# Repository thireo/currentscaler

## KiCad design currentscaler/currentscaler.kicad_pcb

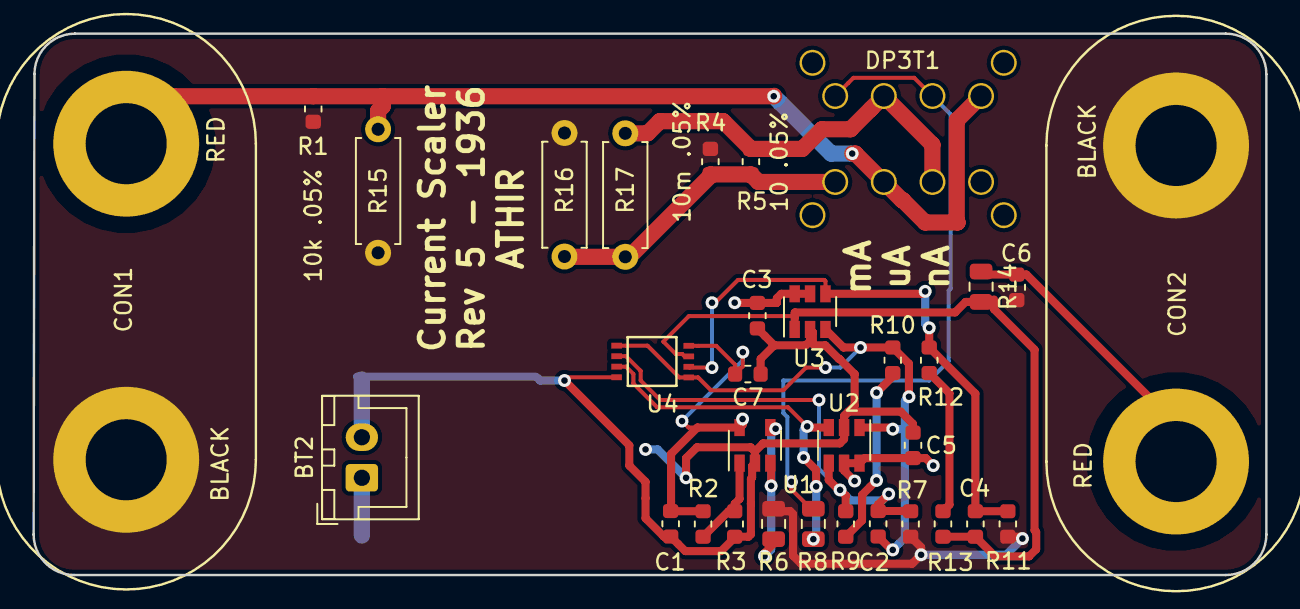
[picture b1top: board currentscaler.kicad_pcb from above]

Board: 2 copper layers, 76.1 x 33.4 mm, 33 parts (1 on the bottom side), 17 nets.

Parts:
BT1: Battery_Cell; R_4020_10251Metric
BT2: Battery_Cell; JST_XH_B2B-XH-A_1x02_P2.50mm_Vertical
C1, C3, C5, C6, C7: 100nF; C_0603_1608Metric
C2, C4: 10p; C_0603_1608Metric
CON1, CON2: RS677-8759; 6778759
DP3T1: OS203013MT6QN1
R1: 10k .05%; R_0603_1608Metric
R2, R3: 100k 1%; R_0603_1608Metric
R4: 10m .05%; R_0603_1608Metric
R5: 10 .05%; R_0603_1608Metric
R6, R8, R14: 220; R_0805_2012Metric
R7, R11: 1k .05%; R_0603_1608Metric
R9, R12: 6.8k .05%; R_0603_1608Metric
R10, R13: 2.2k .05%; R_0603_1608Metric
R15: 10k .05%; R_Axial_DIN0207_L6.3mm_D2.5mm_P7.62mm_Horizontal
R16: 10m .05%; R_Axial_DIN0207_L6.3mm_D2.5mm_P7.62mm_Horizontal
R17: 10 .05%; R_Axial_DIN0207_L6.3mm_D2.5mm_P7.62mm_Horizontal
U1: LMV321; SOT-23-5
U2, U3: MAX4239AUT; SOT-23-6
U4: MAX44246; uMAX8

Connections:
+5V: BT1.1, BT2.1, C1.1, C3.1, C5.1, C7.2, R2.1, U1.5, U2.5, U2.6, U3.5, U3.6, U4.8
GND: BT1.2, BT2.2, C1.2, C3.2, C5.2, C7.1, R3.2, U1.2, U2.2, U3.2, U4.4
GNDREF: C6.2, CON1.2, CON2.2, R1.2, R4.2, R6.1, R7.1, R11.1, R15.2, R16.2
unnamed: C2.1, R10.1, U2.1, U3.3, U4.1, U4.5
unnamed: C2.2, R7.2, R9.2, U2.4, U4.2
unnamed: C4.1, R13.1, R14.2, U3.1, U4.7
unnamed: C4.2, R11.2, R12.2, U3.4, U4.6
unnamed: C6.1, CON2.1, R14.1
unnamed: CON1.1, DP3T1.3, DP3T1.5, R1.1, R15.1
unnamed: DP3T1.2, DP3T1.7, R5.1, R17.1
unnamed: DP3T1.4, R4.1, R5.2, R16.1, R17.2
unnamed: DP3T1.6, DP3T1.8, R8.2
unnamed: R2.2, R3.1, U1.1
unnamed: R6.2, U1.3, U1.4
unnamed: R8.1, U2.3, U4.3
unnamed: R9.1, R10.2
unnamed: R12.1, R13.2

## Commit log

2019-01-27 Initial HW commit
2019-01-30 temp commit
2019-01-31 Started PCB
    Designing for Hammond 1550Q.
2019-03-27 HW: rev 1 - Gerbers
2019-04-01 HW: rev 2 - Gerbers
    Corrected DP3T footprint.
    Added 3D file for entire PCB.
2019-04-01 HW: rev 2 - Gerbers
    Corrected DP3T footprint.
    Added 3D file for entire PCB.
    Made subfoldes for HW revisions.
2019-05-27 WIP: HW4
    100 ohm resistors now 0805.
    Fixed footprint of switch.
    Removed 3V CR2450 holder.
    Added silkscreen explanations.
2019-07-14 HW 4 - commit
2019-08-22 Addes spice file
2019-09-07 Rev 5 1936
    Fixed 5V missing on opamp.
    Added duplicate power and resistor pairs.
2020-08-15 Sorry future me...
